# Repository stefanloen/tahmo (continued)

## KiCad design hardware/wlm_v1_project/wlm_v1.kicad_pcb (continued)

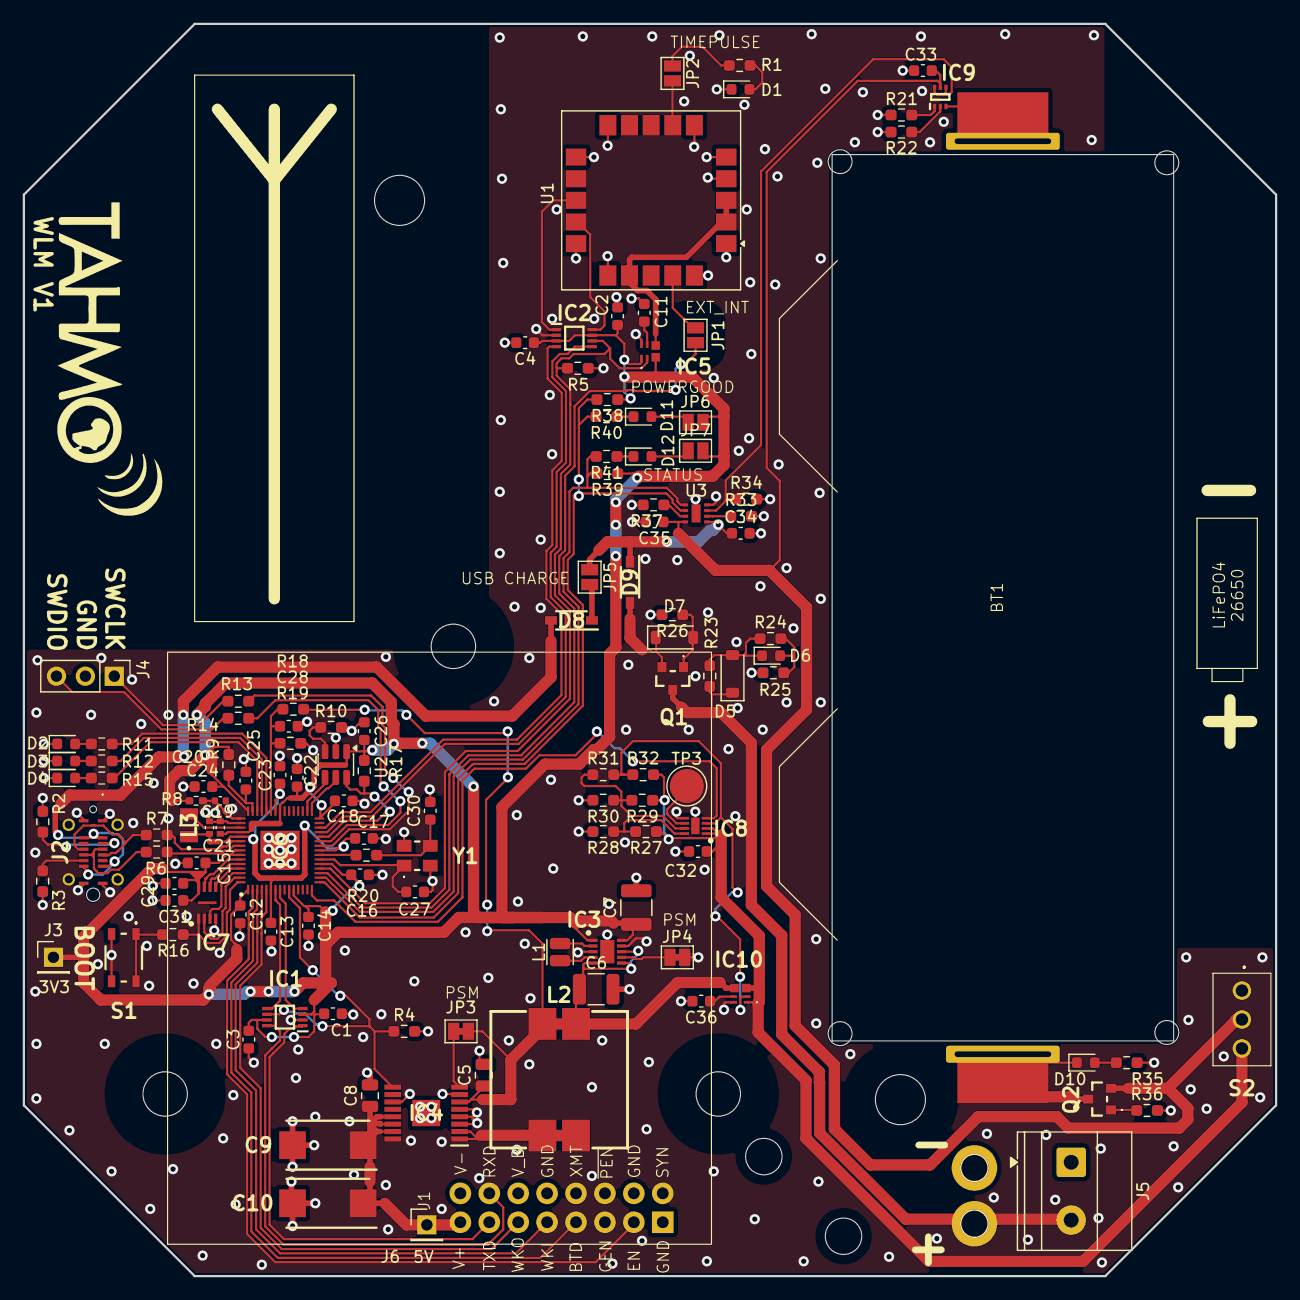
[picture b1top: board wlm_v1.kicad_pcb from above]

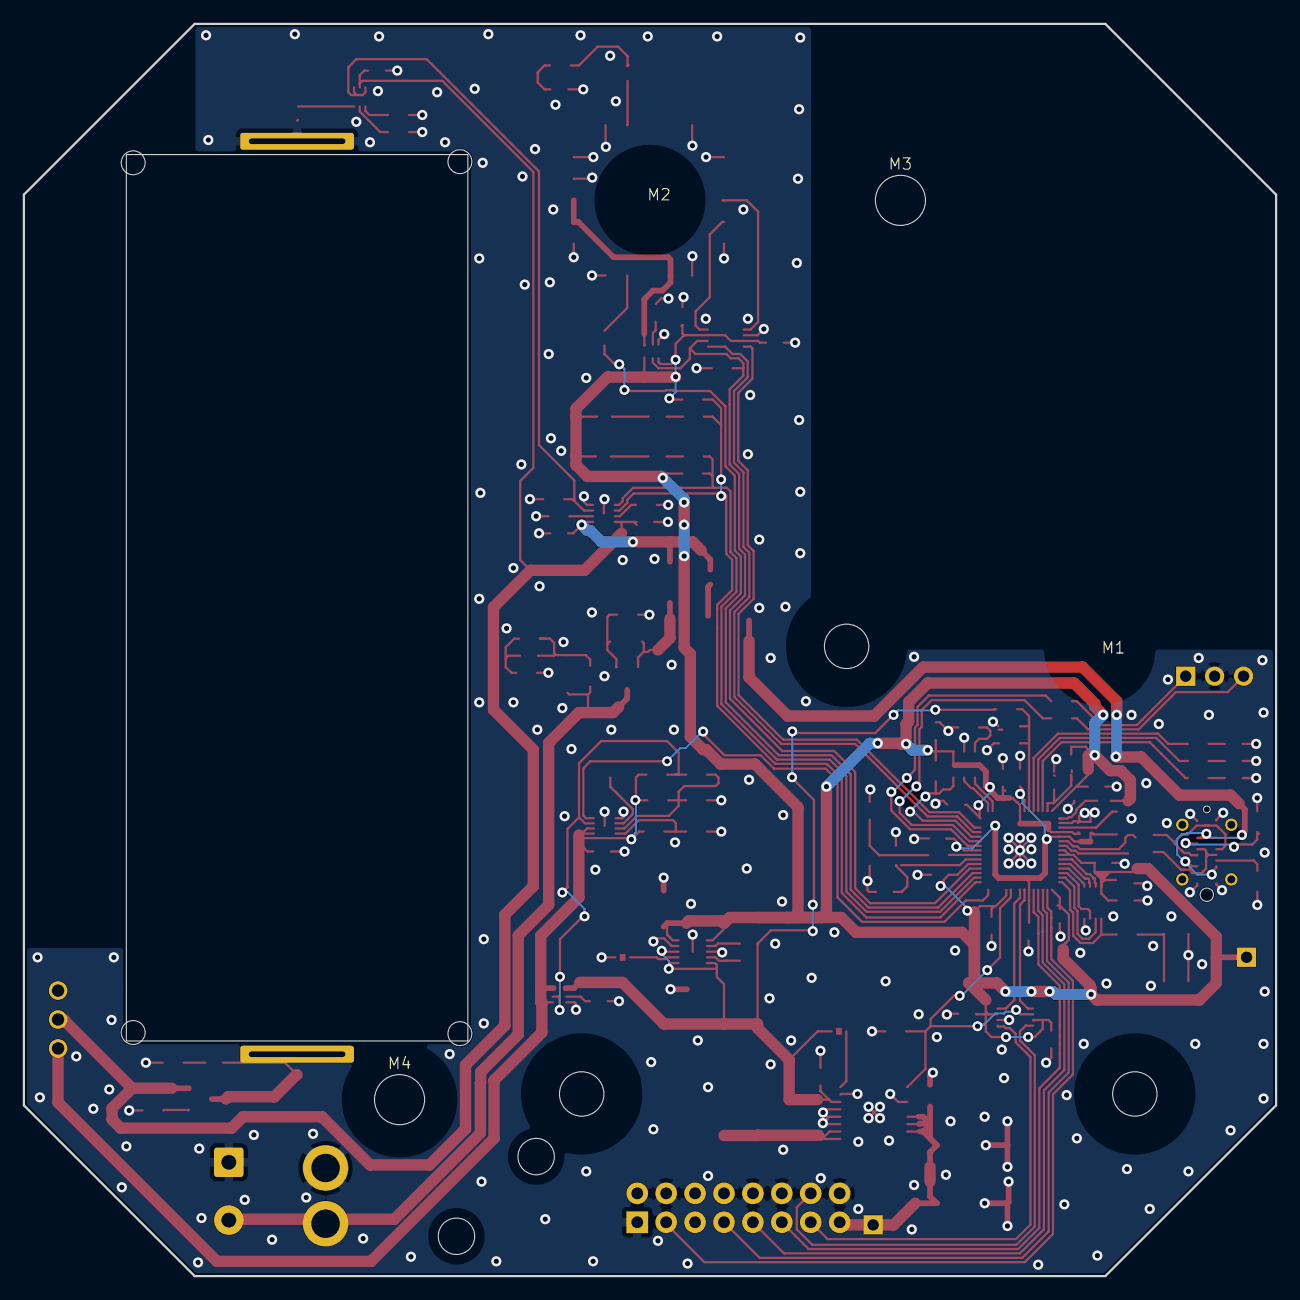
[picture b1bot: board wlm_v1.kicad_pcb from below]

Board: 2 copper layers, 110.0 x 110.0 mm, 137 parts (4 on the bottom side), 95 nets.

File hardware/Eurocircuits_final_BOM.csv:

"Reference:","E1789734"
"Date:","Tue Jun 30 2026 15:51:00 GMT+0200 (Midden-Europese zomertijd)"
"Generated by:","Eurocircuits PCBA Visualizer"

"Reference designators","Quantity","MPN","Manufacturer","Description"
"C1, C2, C3, C4, C12, C13, C14, C15, C16, C18, C20, C22, C23, C26, C29","15","GPC0603104-25","Generic part","0.1µF ±10% 25V Ceramic Capacitor X7R 0603 (1608 Metric)"
"C32, C33","2","GPC0603104-25","Generic part","0.1µF ±10% 25V Ceramic Capacitor X7R 0603 (1608 Metric)"
"C5","1","GPC0805106-25","Generic part","10µF ±10% 25V Ceramic Capacitor X5R 0805 (2012 Metric)"
"C6, C7","2","GPC1210476-16","Generic part","47µF ±20% 16V Ceramic Capacitor X5R 1210 (3225 Metric)"
"C8","1","GPC0805225-25-X7R","Generic part","2.2µF ±10% 25V Ceramic Capacitor X7R 0805 (2012 Metric)"
"C11, C36","2","GPC0603103","Generic part","10000pF ±10% 50V Ceramic Capacitor X7R 0603 (1608 Metric)"
"C17, C25, C31","3","GPC0603475-10","Generic part","4.7µF ±10% 10V Ceramic Capacitor X5R 0603 (1608 Metric)"
"C19, C21, C24","3","GPC0402475-6.3","Generic part","4.7µF ±20% 6.3V Ceramic Capacitor X5R 0402 (1005 Metric)"
"C27, C30","2","GPC0603150","Generic part","15pF ±5% 50V Ceramic Capacitor C0G, NP0 0603 (1608 Metric)"
"C28","1","GPC0603102-25","Generic part","1000pF ±10% 25V Ceramic Capacitor X7R 0603 (1608 Metric)"
"C34, C35","2","GPC0603105","Generic part","1µF ±10% 50V Ceramic Capacitor X5R 0603 (1608 Metric)"
"R1","1","GPR06032K","Generic part","0603, Res 2.0kOhm, 75V, 1.0%, 100mW"
"R2, R3","2","GPR06035K1","Generic part","0603, Res 5.1kOhm, 75V, 1.0%, 100mW"
"R4, R5, R17, R26, R32, R36","6","GPR0603100K","Generic part","0603, Res 100.0kOhm, 50V, 1.0%, 100mW"
"R37","1","GPR0603100K","Generic part","0603, Res 100.0kOhm, 50V, 1.0%, 100mW"
"R18, R19","2","GPR0603100K","Generic part","0603, Res 100.0kOhm, 50V, 1.0%, 100mW"
"R6, R7","2","GPR060327R","Generic part","0603, Res 27.0Ohm, 75V, 1.0%, 100mW"
"R8","1","GPR040233R","Generic part","0402, Res 33.0Ohm, 50V, 1.0%, 62.5mW"
"R9","1","GPR0603200R","Generic part","0603, Res 200.0Ohm, 50V, 1.0%, 100mW"
"R10","1","GPR060322K","Generic part","0603, Res 22.0kOhm, 50V, 1.0%, 100mW"
"R11, R12, R15, R35, R40, R41","6","GPR06031K","Generic part","0603, Res 1.0kOhm, 50V, 1.0%, 100mW"
"R16, R20","2","GPR06031K","Generic part","0603, Res 1.0kOhm, 50V, 1.0%, 100mW"
"R13, R14","2","GPR0603100R","Generic part","0603, Res 100.0Ohm, 50V, 1.0%, 100mW"
"R21","1","GPR06039K1","Generic part","0603, Res 9.1kOhm, 75V, 1.0%, 100mW"
"R23","1","GPR06032M2","Generic part","0603, Res 2.2MOhm, 75V, 1.0%, 100mW"
"R24","1","GPR0603220K","Generic part","0603, Res 220.0kOhm, 75V, 1.0%, 100mW"
"R25","1","GPR06035K6","Generic part","0603, Res 5.6kOhm, 50V, 1.0%, 100mW"
"R31","1","GPR06031M5","Generic part","0603, Res 1.5MOhm, 75V, 1.0%, 100mW"
"R33","1","GPR0603620R","Generic part","0603, Res 620.0Ohm, 75V, 1.0%, 100mW"
"R34","1","GPR060310K","Generic part","0603, Res 10.0kOhm, 50V, 1.0%, 100mW"
"R38, R39","2","GPR060310K","Generic part","0603, Res 10.0kOhm, 50V, 1.0%, 100mW"
"D1, D12","2","LTST-C191KFKT","Lite-On","Orange 605nm LED Indication - Discrete 2V 0603 (1608 Metric)"
"D2, D6, D10","3","LTST-C193KRKT-5A","Lite-On","Red 631nm LED Indication - Discrete 2V 0603"
"D3, D11","2","LTST-C193KGKT-5A","Lite-On","Green 572nm LED Indication - Discrete 2V 0603 (1608 Metric)"
"D4","1","LTST-C190TBKT","Lite-On","Blue 470nm LED Indication - Discrete 3.3V 0603 (1608 Metric)"
"D5","1","1N4148W","Vishay","Small Signal Fast Switching Diode SOD-123 SMD DIODE 75V /125mA"
"D7","1","BZT52C5V6-7-F","Diodes Inc.","Zener Diode 5.6V 500mW ±7% Surface Mount SOD-123"
"J5","1","691213510002","Wurth Elektronik","2 Position Wire to Board Terminal Block Horizontal with Board 0.200"" (5.08mm) Through Hole"
"L1","1","74479276222C","Wurth Elektronik","2.2µH Shielded Molded Inductor 1.6A 135 mOhm Max 0806 (2016 Metric)"
"R28, R30","2","RC0603FR-0749K9L","Yageo","RES 49.9K OHM 1% 1/10W 0603"
"BT1","1","Keystone_1106","Keystone Electronics","Battery Holder 26650 1 Cell SMD (SMT) Tab"
"C9","1","TR3E227M016C0100","Vishay Sprague","220 µF ±20% Molded Tantalum Capacitors 16 V 2917 (7343 Metric) 100mOhm @ 100kHz"
"D8, D9","2","MBR120LSFT1G","ON Semiconductor","Diode Schottky 20V 1A Surface Mount SOD-123L"
"IC1, IC2","2","TXU0202DCUR","Texas Instruments","Two channel fixed-direction level shifter with channels in opposite direction 8-VSSOP -40 to 125"
"IC3","1","RT6150B-33GQW","Richtek USA Inc.","Buck-Boost Switching Regulator IC Positive Fixed 3.3V 1 Output 800mA 10-WFDFN Exposed Pad"
"IC4","1","TPS61032PWPR","Texas Instruments","Boost Switching Regulator IC Positive Fixed 5V 1 Output 3.6A (Switch) 16-PowerTSSOP (0.173"", 4.40mm Width)"
"IC5, IC10","2","SLG59M309V","Renesas","Power Switch/Driver 1:1 N-Channel 4A 8-FC-TDFN (1.5x2)"
"IC6","1","RP2350A-CT","Raspberry Pi","MCU, 32 bit, ARM Cortex-M33F, 150 MHz, 520 KB RAM, QFN-60"
"IC7","1","W25Q32RVXHJQ TR","Winbond Electronics","Serial NOR Flash, QSPI, 32MBit, 8-pin USON 2x3mm 133MHz"
"IC8","1","LTC2960IDC-1#TRMPBF","Analog Devices","Supervisor Open Drain or Open Collector 2 Channel 8-DFN (2x2)"
"IC9","1","TMP390A3DRLR","Texas Instruments","Thermostat Programmable Active Low Open Drain"
"J1","1","ESW-108-58-S-D","Samtec","16 Position Elevated Socket Connector 0.100"" (2.54mm) Through Hole Gold"
"J2","1","2193200001","Molex","USB-C (USB TYPE-C) USB 2.0 Receptacle Connector 24 (16+8 Dummy) Position Surface Mount, Through Hole"
"L2","1","CDRH124NP-6R8MC","Sumida","6.8 µH Shielded Inductor 4.9 A,  ±20%, 23mOhm Max Nonstandard"
"L3","1","AOTA-B201610S3R3-101-T","Abracon","3.3 µH ±20% Shielded Molded Inductor 2.1 A 140mOhm Max 0806 (2016 Metric)"
"Q1, Q2","2","DMP2035U-7","Diodes Inc.","Transistor, P-Channel Enhancement Mode MOSFET, SMD"
"R22","1","RMCF0603FT21K5","Stackpole Electronics","21.5 kOhms ±1% 0.1W, 1/10W Chip Resistor 0603 (1608 Metric) Automotive AEC-Q200 Thick Film"
"R27","1","RT0603DRE07340KL","Yageo","340 kOhms ±0.5% 0.1W, 1/10W Chip Resistor 0603 (1608 Metric) Thin Film"
"R29","1","RMCF0603FT316K","Stackpole Electronics","316 kOhms ±1% 0.1W, 1/10W Chip Resistor 0603 (1608 Metric) Automotive AEC-Q200 Thick Film"
"S1","1","PTS810SJK250SMTRLFS","C&K Components","Tactile Switch SPST-NO Top Actuated Surface Mount"
"S2","1","200AWMSP1T2A1M2RE","E-Switch","Toggle Switch SPDT Through Hole"
"U1","1","SAM-M10Q-00B","U-Blox","- RF Receiver Galileo, GLONASS, GPS 1.575GHz, 1.602GHz -165dBm 400kbps On-Board, Patch Module"
"U2","1","TPL5010DDCR","Texas Instruments","Programmable Timer IC  TSOT-23-6"
"U3","1","BQ25176MDSGR","Texas Instruments","800-mA linear battery charger for one-cell Li-ion and LiFePO4 with VINDPM 8-WSON -40 to 125"
"Y1","1","ABM8-272-T3","Abracon","12 MHz ±30ppm Crystal 10 pF 50 Ohms 4-SMD, No Lead"

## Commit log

2025-12-18 add usb from example
2025-12-18 move usb to separate files
2025-12-18 Usb chipID as serial number
2025-12-18 Implement command structure
2025-12-20 Clean up usb coms.
2025-12-20 Enable batvolt command
2025-12-20 Enable getconst command
2026-02-17 Update pins to prototype
2026-02-18 Upgrade interface
2026-02-18 GhanaV1
2026-02-19 add status update via usb
2026-02-19 store config in flash
2026-02-21 add parser page
2026-02-21 rename to docs
2026-02-21 oops
2026-02-21 Rename to index.html
2026-02-21 Update parser
2026-02-21 update pins
2026-03-14 Store and comm boot counts
2026-04-03 Update online decoder
2026-05-19 Initial add of wlm_v1 pcb + documentation
2026-06-09 Update pins + watchdog
2026-06-25 Add get temperature from usb
2026-06-25 Add RGB leds
2026-06-28 Update chargestate
2026-06-28 Allow selecting of thing in webpage
2026-06-28 Add online serial monitor
2026-06-29 Download raw data
2026-06-29 Mobile browser fix?
2026-06-29 program page
2026-06-29 case sensitive typo
2026-06-29 Streamline webpages
2026-06-29 Transmit start and end time
2026-06-29 Update GitHub Actions workflow for firmware build
2026-06-29 Update picotool installation method in workflow
    Replaced the build process of picotool from source compilation to installation of a pre-compiled binary.
2026-06-29 Revise picotool installation to build from source
    Updated the workflow to build and install picotool from source instead of using a pre-compiled binary.
2026-06-29 Fix path for UF2 conversion in build workflow
2026-06-29 Enable automatic UF2 file commit and push
    Added permissions for write access and implemented automatic commit and push of the generated UF2 file to the main branch after conversion.
2026-06-29 Automated firmware deployment [skip ci]
2026-06-30 Update UF2 file path in build workflow
2026-06-30 Cleanup
2026-06-30 Add eurocircuits BOM
2026-06-30 Update build_firmware.yml to limit paths
    Restrict workflow triggers to changes in the 'control' directory.
2026-06-30 Update flash page
